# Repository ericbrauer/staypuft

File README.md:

# staypuft
A Big Muff clone with some points open for modding.

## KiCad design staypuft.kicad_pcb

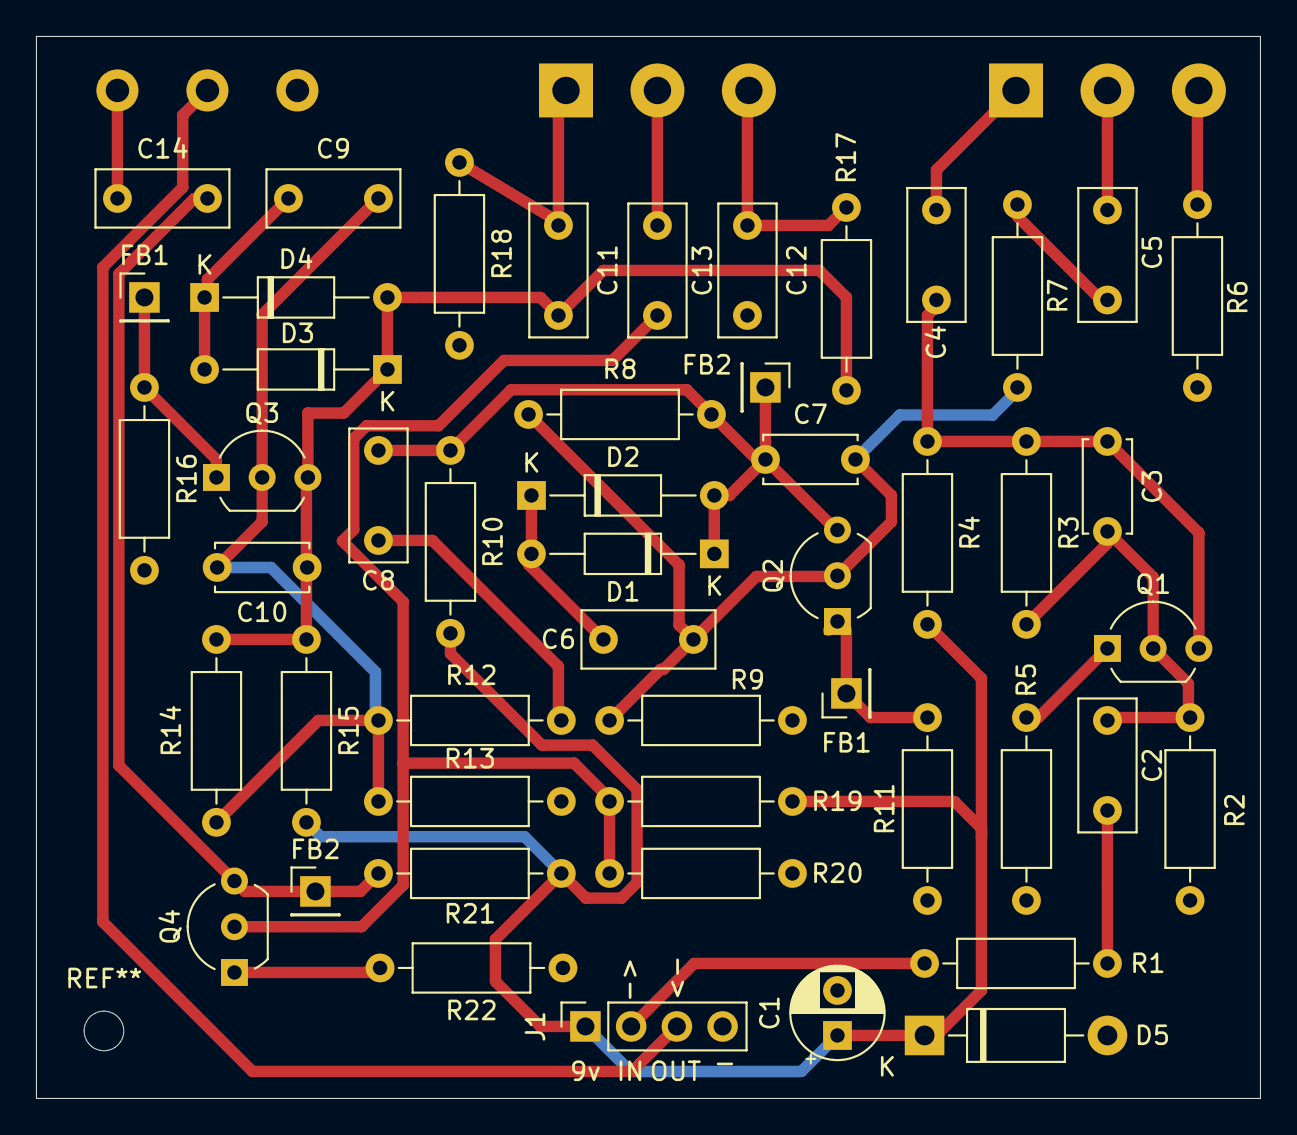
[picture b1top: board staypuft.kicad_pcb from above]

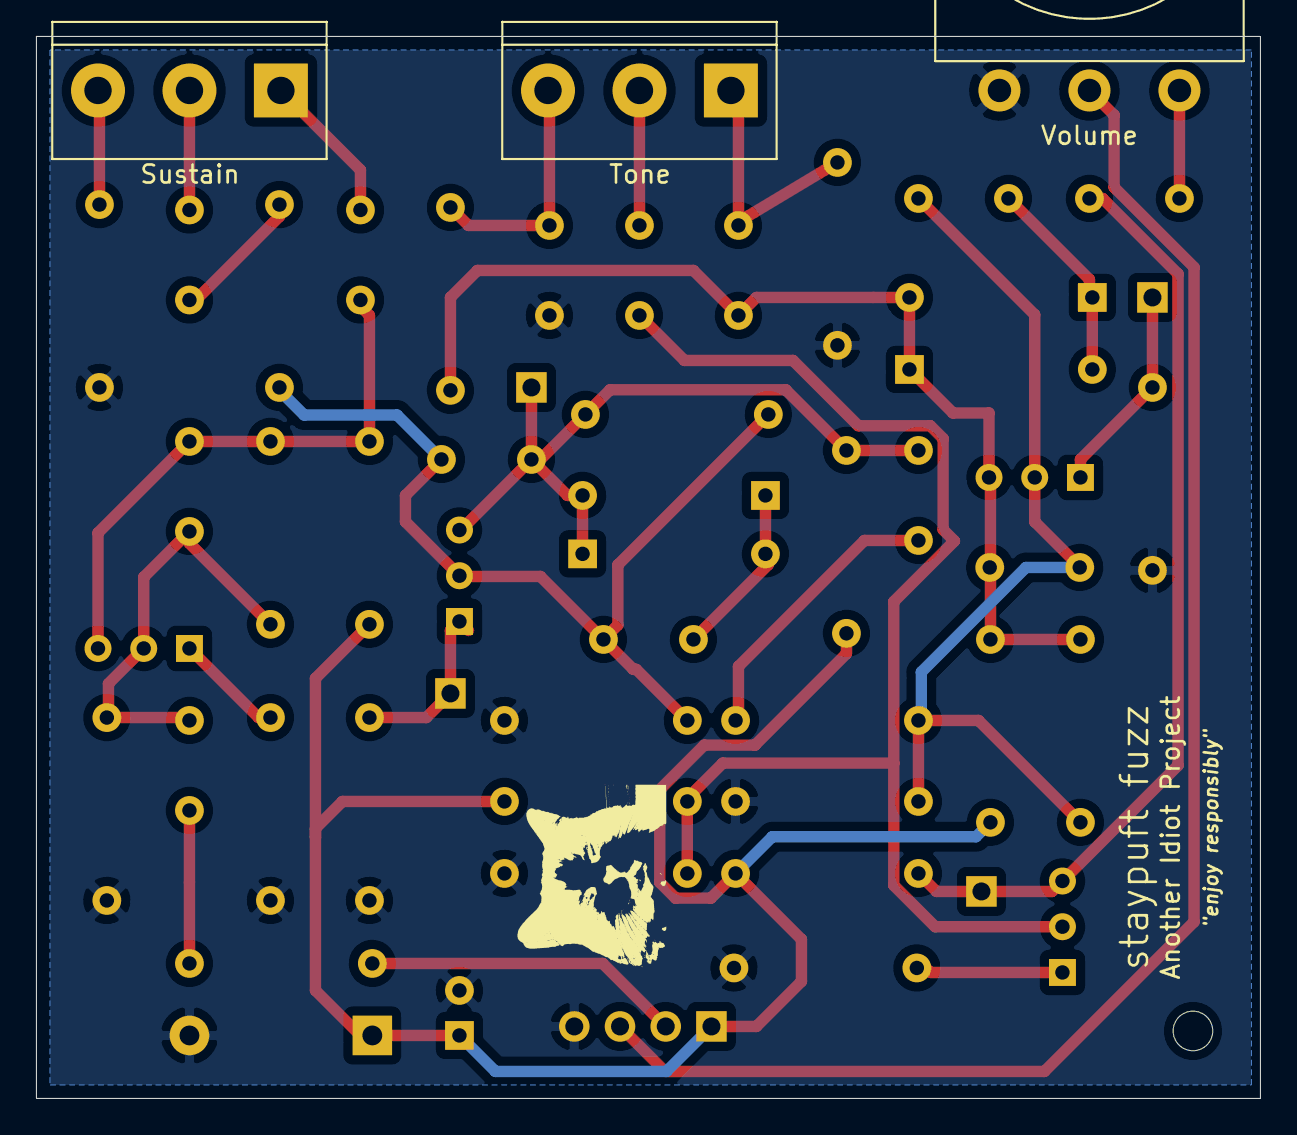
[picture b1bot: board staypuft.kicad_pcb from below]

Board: 2 copper layers, 68.0 x 59.0 mm, 53 parts (3 on the bottom side), 28 nets.

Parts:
C1: 20u; CP_Radial_D5.0mm_P2.50mm
C2, C4, C5, C8, C13, C14: 100n; C_Rect_L7.2mm_W3.0mm_P5.00mm_FKS2_FKP2_MKS2_MKP2
C3, C7, C10: 470p; C_Disc_D5.0mm_W2.5mm_P5.00mm
C6, C9: 47n; C_Rect_L7.2mm_W3.0mm_P5.00mm_FKS2_FKP2_MKS2_MKP2
C11: 3.9n; C_Rect_L7.2mm_W3.0mm_P5.00mm_FKS2_FKP2_MKS2_MKP2
C12: 10n; C_Rect_L7.2mm_W3.0mm_P5.00mm_FKS2_FKP2_MKS2_MKP2
D1, D2, D3, D4: 1N914; D_DO-35_SOD27_P10.16mm_Horizontal
D5: 1n4001; D_DO-41_SOD81_P10.16mm_Horizontal
FB1, FB1#2, FB2, FB2#2: TestPoint; PinHeader_1x01_P2.54mm_Vertical
J1: Conn_01x04_Male; PinSocket_1x04_P2.54mm_Vertical
Q1, Q2, Q3, Q4: 2N5088; TO-92_Inline_Wide
R1: 39k; R_Axial_DIN0207_L6.3mm_D2.5mm_P10.16mm_Horizontal
R2, R9, R13, R20: 100k; R_Axial_DIN0207_L6.3mm_D2.5mm_P10.16mm_Horizontal
R3, R8, R14, R19: 470k; R_Axial_DIN0207_L6.3mm_D2.5mm_P10.16mm_Horizontal
R4, R10, R15: 12k; R_Axial_DIN0207_L6.3mm_D2.5mm_P10.16mm_Horizontal
R5, R11, R16: 390; R_Axial_DIN0207_L6.3mm_D2.5mm_P10.16mm_Horizontal
R6: 1k; R_Axial_DIN0207_L6.3mm_D2.5mm_P10.16mm_Horizontal
R7, R12, R21: 10k; R_Axial_DIN0207_L6.3mm_D2.5mm_P10.16mm_Horizontal
R17: 20k; R_Axial_DIN0207_L6.3mm_D2.5mm_P10.16mm_Horizontal
R18: 22k; R_Axial_DIN0207_L6.3mm_D2.5mm_P10.16mm_Horizontal
R22: 2.7k; R_Axial_DIN0207_L6.3mm_D2.5mm_P10.16mm_Horizontal
RV3: 100k; Potentiometer_Omeg_PC16BU_Vertical
Sustain: 100k; TerminalBlock_bornier-3_P5.08mm
Tone: 100k; TerminalBlock_bornier-3_P5.08mm

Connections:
unnamed: C2.1, C3.2, Q1.2, R2.2, R3.2
unnamed: C2.2, R1.1
unnamed: C3.1, C4.2, Q1.3, R3.1, R4.1
unnamed: C4.1, Sustain.1
unnamed: C5.1, R7.1
unnamed: C5.2, Sustain.2
unnamed: C6.1, D1.2, D2.1
unnamed: C6.2, C7.2, Q2.2, R7.2, R8.2, R9.2
unnamed: C7.1, C8.2, D1.1, D2.2, FB2.1, Q2.3, R8.1, R10.1
unnamed: C8.1, R12.1
unnamed: C9.1, D3.2, D4.1
unnamed: C10.1, C11.2, D3.1, D4.2, Q3.3, R14.1, R15.1, R17.2
unnamed: C9.2, C10.2, Q3.2, R12.2, R13.1, R14.2
unnamed: C11.1, R18.1, Tone.1
unnamed: C12.2, R17.1, Tone.3
unnamed: C13.1, Q4.2, R19.1, R20.2
unnamed: C13.2, Tone.2
unnamed: C14.1, RV3.1
unnamed: C14.2, FB2#2.1, Q4.3, R21.1
unnamed: Q1.1, R5.2
unnamed: FB1.1, Q2.1, R11.2
unnamed: FB1#2.1, Q3.1, R16.1
unnamed: Q4.1, R22.2
unnamed: R6.2, Sustain.3
gnd: C1.2, C12.1, D5.2, J1.4, R2.1, R5.1, R6.1, R9.1, R11.1, R13.2, R16.2, R18.2, R20.1, R22.1, RV3.3
in: J1.2, R1.2
out: J1.3, RV3.2
pwr: C1.1, D5.1, J1.1, R4.2, R10.2, R15.2, R19.2, R21.2

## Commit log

2021-05-01 initial schematic finished
2021-05-01 updated values
2021-05-01 choosing footprints
2021-05-04 finished footprint association
2021-05-04 inital pcb layout started, design rules set
2021-05-06 grouping on pcb in prog
2021-05-14 still working on pcb
2021-05-14 rough pcb done, align todo
2021-05-14 final touches done on pcb
2021-05-14 added schematic
